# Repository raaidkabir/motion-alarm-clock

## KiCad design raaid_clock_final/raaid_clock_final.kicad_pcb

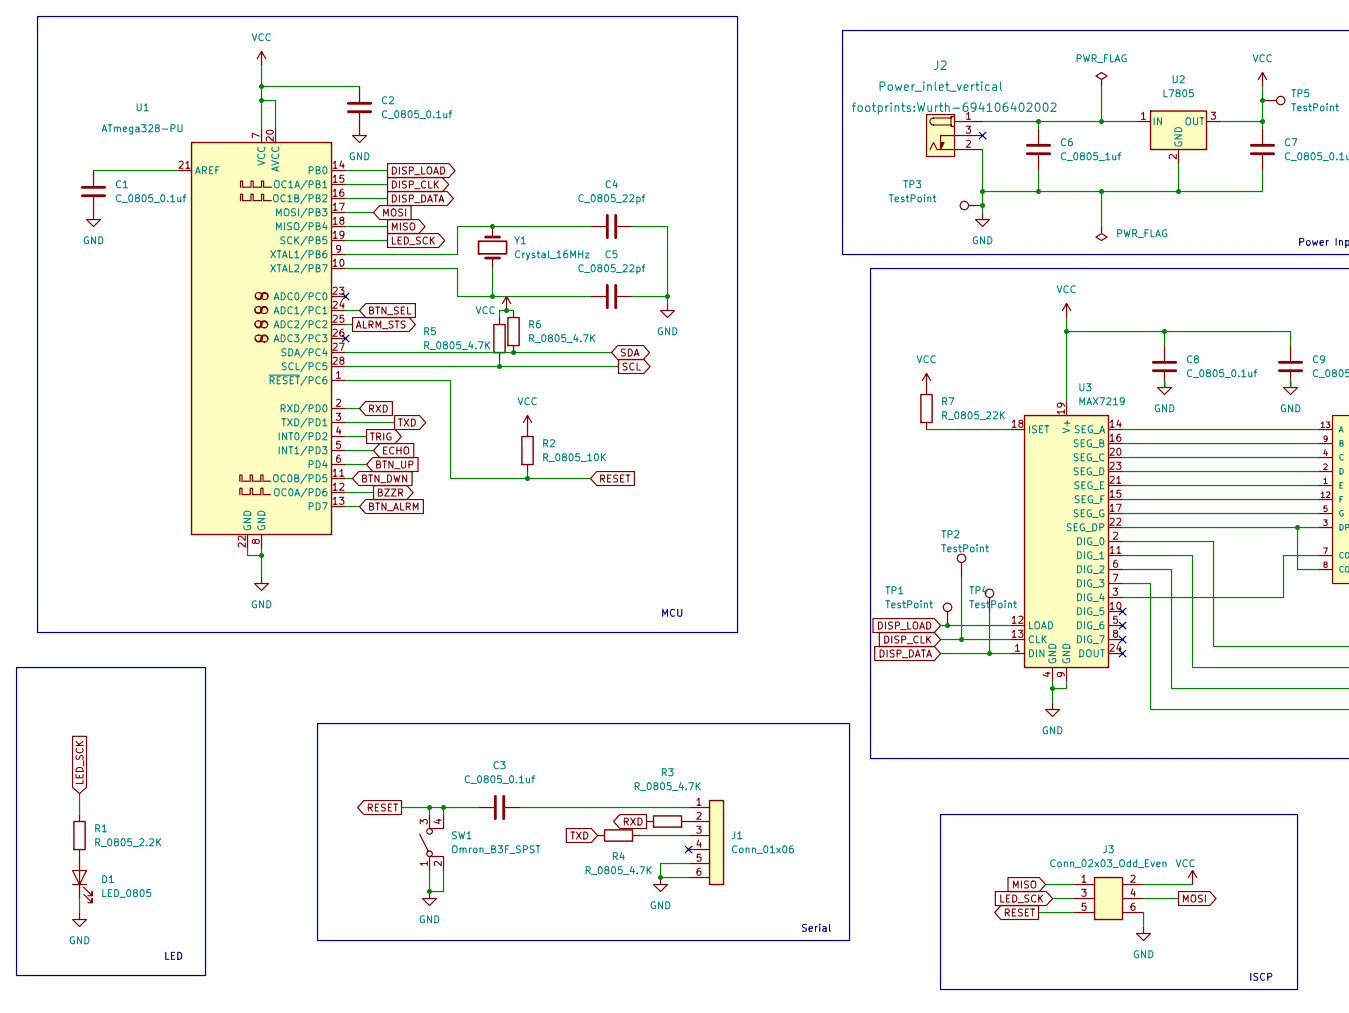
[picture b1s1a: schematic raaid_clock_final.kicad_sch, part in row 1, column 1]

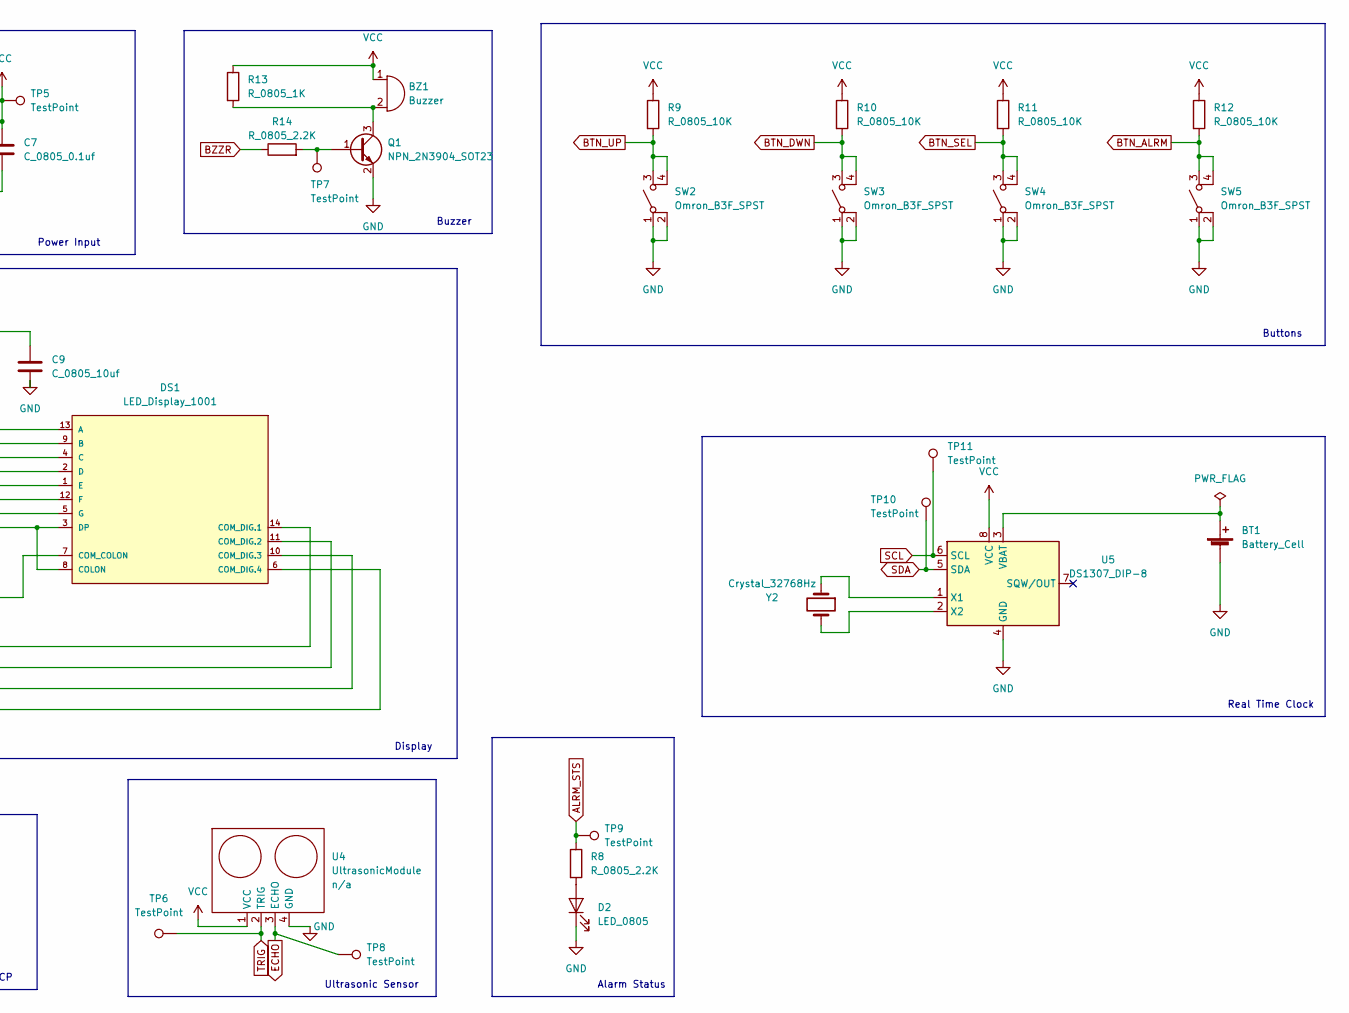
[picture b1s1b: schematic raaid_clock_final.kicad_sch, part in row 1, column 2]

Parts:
BT1: Battery_Cell; BatteryHolder_Keystone_106_1x20mm; MPN BS-7; Digikey PN BS-7-ND
BZ1: Buzzer; Buzzer_TDK_PS1240P02BT_D12.2mm_H6.5mm; MPN PS1420P02CT; Digikey PN 445-2526-1-ND
C1, C2, C3, C7, C8: C_0805_0.1uf; C_0805_2012Metric; Voltage N/A; Tolerance N/A; MPN 08055C104KAT2A; Digikey PN 478-1395-1-ND
C4, C5: C_0805_22pf; C_0805_2012Metric; Voltage N/A; Tolerance N/A; MPN CC0805JRNPO9BN220; Digikey PN 311-1103-1-ND
C6: C_0805_1uf; C_0805_2012Metric; Voltage N/A; Tolerance N/A; MPN CC0805KKX7R8BB105; Digikey PN 311-1456-1-ND
C9: C_0805_10uf; C_0805_2012Metric; Voltage N/A; Tolerance N/A; MPN GRM21BR61E106KA73L; Digikey PN 490-5523-1-ND
D1, D2: LED_0805; LED_0805_2012Metric; MPN 150080RS75000; Digikey PN 732-4984-1-ND
DS1: LED_Display_1001; Adafruit-1001-0-0-MFG; forward voltage 3.2V; reverse voltage 5V; mouser part number 485-1001; digikey description WHITE 7-SEGMENT CLOCK DISPLAY
J1: Conn_01x06; PinHeader_1x06_P2.54mm_Vertical; MPN 61300611121; Digikey PN 732-5319-ND
J2: Power_inlet_vertical; Wurth-694106402002; MPN 694106402002; Digikey PN 732-5931-ND
J3: Conn_02x03_Odd_Even; PinHeader_2x03_P2.54mm_Vertical; MPN PRPC003DAAN-RC; Digikey PN S2011EC-03-ND
Q1: NPN_2N3904_SOT23; SOT-23; MPN CMPT3904E TR PBFREE; Digikey PN 1514-CMPT3904ETRPBFREECT-ND
R1, R8, R14: R_0805_2.2K; R_0805_2012Metric; Tolerance N/A; MPN N/A; Digikey PN 311-2.20KCRCT-ND
R2, R9, R10, R11, R12: R_0805_10K; R_0805_2012Metric; Tolerance N/A; MPN RC0805FR-0710KL; Digikey PN 311-10.0KCRCT-ND
R3, R4, R5, R6: R_0805_4.7K; R_0805_2012Metric; Tolerance N/A; MPN RC0805FR-074K7L; Digikey PN 311-4.70KCRCT-ND
R7: R_0805_22K; R_0805_2012Metric; Tolerance N/A; MPN RC0805FR-0722KL; Digikey PN 311-22.0KCRCT-ND
R13: R_0805_1K; R_0805_2012Metric; Tolerance N/A; Mouser PN N/A; Digikey PN RC0805FR-0710KL
SW1, SW2, SW3, SW4, SW5: Omron_B3F_SPST; SW_SPST_Omron_B3FS-100xP; MPN B3FS-1000P; Digikey PN SW423CT-ND
TP1, TP2, TP3, TP4, TP5, TP6, TP7, TP8, TP9, TP10, TP11: TestPoint; TestPoint_THTPad_D2.0mm_Drill1.0mm
U1: ATmega328-PU; DIP-28_W7.62mm; MPN ED281DT; Digikey PN ED3050-5-ND
U2: L7805; TO-252-2; MPN L7805CDT-TR; Digikey PN 497-7255-1-ND
U3: MAX7219; DIP-24_W7.62mm; MPN ED241DT; Digikey PN ED3049-5-ND
U4: UltrasonicModule; HC-SR04_Horiz; Digikey PN n/a
U5: DS1307_DIP-8; DIP-8_W7.62mm; MPN A 08-LC-TT; Digikey PN AE9986-ND
Y1: Crystal_16MHz; Crystal_SMD_HC49-SD; MPN ECS-160-20-5PXDN-TR; Digikey PN XC1299CT-ND
Y2: Crystal_32768Hz; Crystal_SMD_2Pin_3.2x1.5mm; MPN Q 0,032768-JTX310-12,5-20-T1-HMR-50K-LF; Digikey PN 1908-1314-1-ND

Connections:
ALRM_STS: R8.1, TP9.1, U1.25 (ADC2/PC2)
BTN_ALRM: R12.2, SW5.3 (B), SW5.4 (B), U1.13 (PD7)
BTN_DWN: R10.2, SW3.3 (B), SW3.4 (B), U1.11 (OC0B/PD5)
BTN_SEL: R11.2, SW4.3 (B), SW4.4 (B), U1.24 (ADC1/PC1)
BTN_UP: R9.2, SW2.3 (B), SW2.4 (B), U1.6 (PD4)
BZZR: R14.1, U1.12 (OC0A/PD6)
DISP_CLK: TP2.1, U1.15 (OC1A/PB1), U3.13 (CLK)
DISP_DATA: TP4.1, U1.16 (OC1B/PB2), U3.1 (DIN)
DISP_LOAD: TP1.1, U1.14 (PB0), U3.12 (LOAD)
ECHO: TP8.1, U1.5 (INT1/PD3), U4.3 (ECHO)
GND: BT1.2 (-), C1.2, C2.2, C4.2, C5.2, C6.2, C7.2, C8.2, C9.2, D1.1 (K), D2.1 (K), J1.5, J1.6, J2.2 (OUT), J3.6, Q1.2 (E), SW1.1 (A), SW1.2 (A), SW2.1 (A), SW2.2 (A), SW3.1 (A), SW3.2 (A), SW4.1 (A), SW4.2 (A), SW5.1 (A), SW5.2 (A), TP3.1, U1.8 (GND), U1.22 (GND), U2.2 (GND), U3.4 (GND), U3.9 (GND), U4.4 (GND), U5.4 (GND)
LED_SCK: J3.3, R1.1, U1.19 (SCK/PB5)
MISO: J3.1, U1.18 (MISO/PB4)
MOSI: J3.4, U1.17 (MOSI/PB3)
unnamed: BT1.1 (+), U5.3 (VBAT)
unnamed: BZ1.2 (+), Q1.3 (C), R13.2
unnamed: C1.1, U1.21 (AREF)
unnamed: C3.1, J1.1
unnamed: C4.1, U1.9 (XTAL1/PB6), Y1.2
unnamed: C5.1, U1.10 (XTAL2/PB7), Y1.1
unnamed: C6.1, J2.1 (POLE), U2.1 (IN)
unnamed: D1.2 (A), R1.2
unnamed: D2.2 (A), R8.2
unnamed: DS1.1 (E), U3.21 (SEG_E)
unnamed: DS1.2 (D), U3.23 (SEG_D)
unnamed: DS1.3 (DP), DS1.8 (COLON), U3.22 (SEG_DP)
unnamed: DS1.4 (C), U3.20 (SEG_C)
unnamed: DS1.5 (G), U3.17 (SEG_G)
unnamed: DS1.6 (COM_DIG.4), U3.7 (DIG_3)
unnamed: DS1.7 (COM_COLON), U3.3 (DIG_4)
unnamed: DS1.9 (B), U3.16 (SEG_B)
unnamed: DS1.10 (COM_DIG.3), U3.6 (DIG_2)
unnamed: DS1.11 (COM_DIG.2), U3.11 (DIG_1)
unnamed: DS1.12 (F), U3.15 (SEG_F)
unnamed: DS1.13 (A), U3.14 (SEG_A)
unnamed: DS1.14 (COM_DIG.1), U3.2 (DIG_0)
unnamed: J1.2, R3.2
unnamed: J1.3, R4.2
unnamed: Q1.1 (B), R14.2, TP7.1
unnamed: R7.2, U3.18 (ISET)
unnamed: U5.1 (X1), Y2.1
unnamed: U5.2 (X2), Y2.2
RESET: C3.2, J3.5, R2.2, SW1.3 (B), SW1.4 (B), U1.1 (~RESET/PC6)
RXD: R3.1, U1.2 (RXD/PD0)
SCL: R5.2, TP11.1, U1.28 (SCL/PC5), U5.6 (SCL)
SDA: R6.2, TP10.1, U1.27 (SDA/PC4), U5.5 (SDA)
TRIG: TP6.1, U1.4 (INT0/PD2), U4.2 (TRIG)
TXD: R4.1, U1.3 (TXD/PD1)
VCC: BZ1.1 (-), C2.1, C7.1, C8.1, C9.1, J3.2, R2.1, R5.1, R6.1, R7.1, R9.1, R10.1, R11.1, R12.1, R13.1, TP5.1, U1.7 (VCC), U1.20 (AVCC), U2.3 (OUT), U3.19 (V+), U4.1 (VCC), U5.8 (VCC)

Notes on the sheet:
MCU
Buzzer
Power Input
LED
Ultrasonic Sensor
Alarm Status
ISCP
Display
Serial
Real Time Clock
Buttons

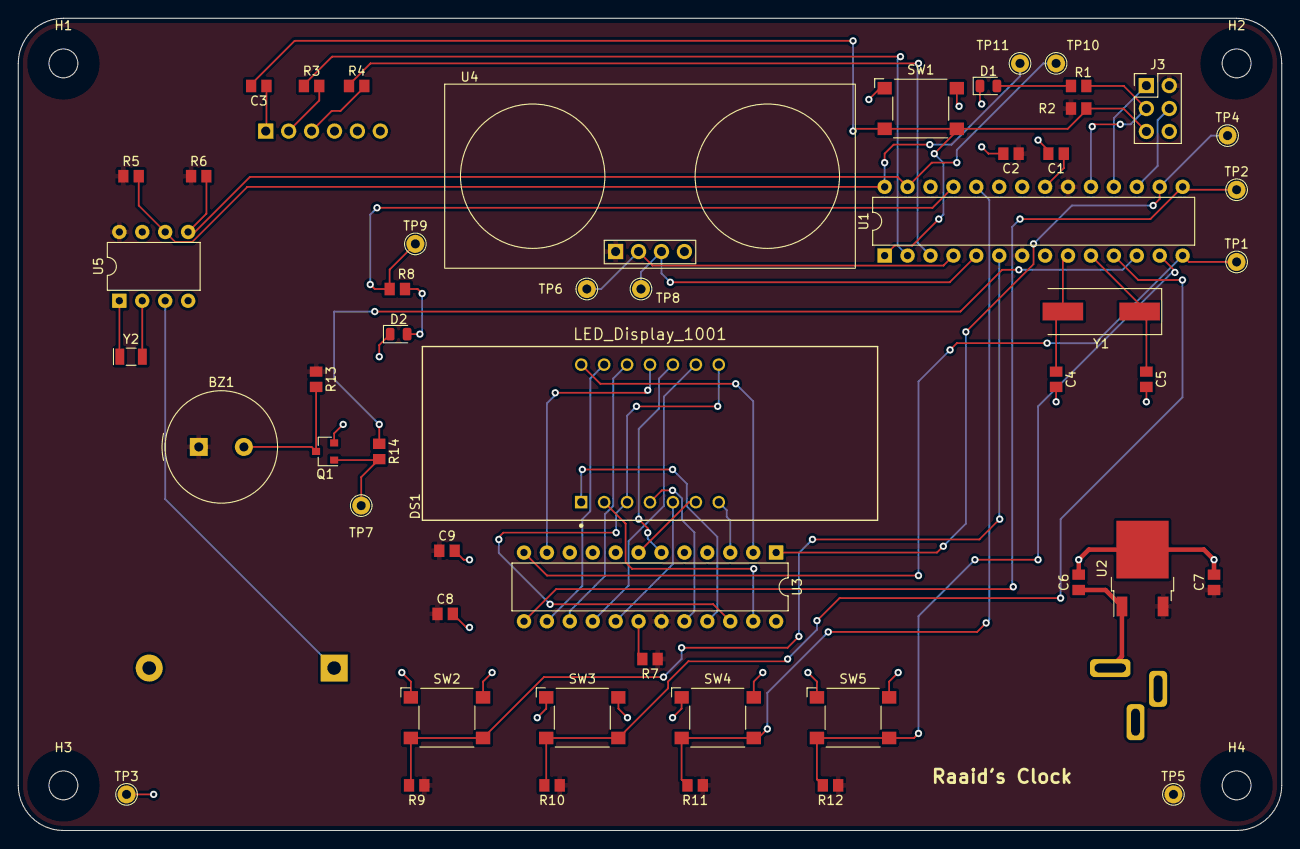
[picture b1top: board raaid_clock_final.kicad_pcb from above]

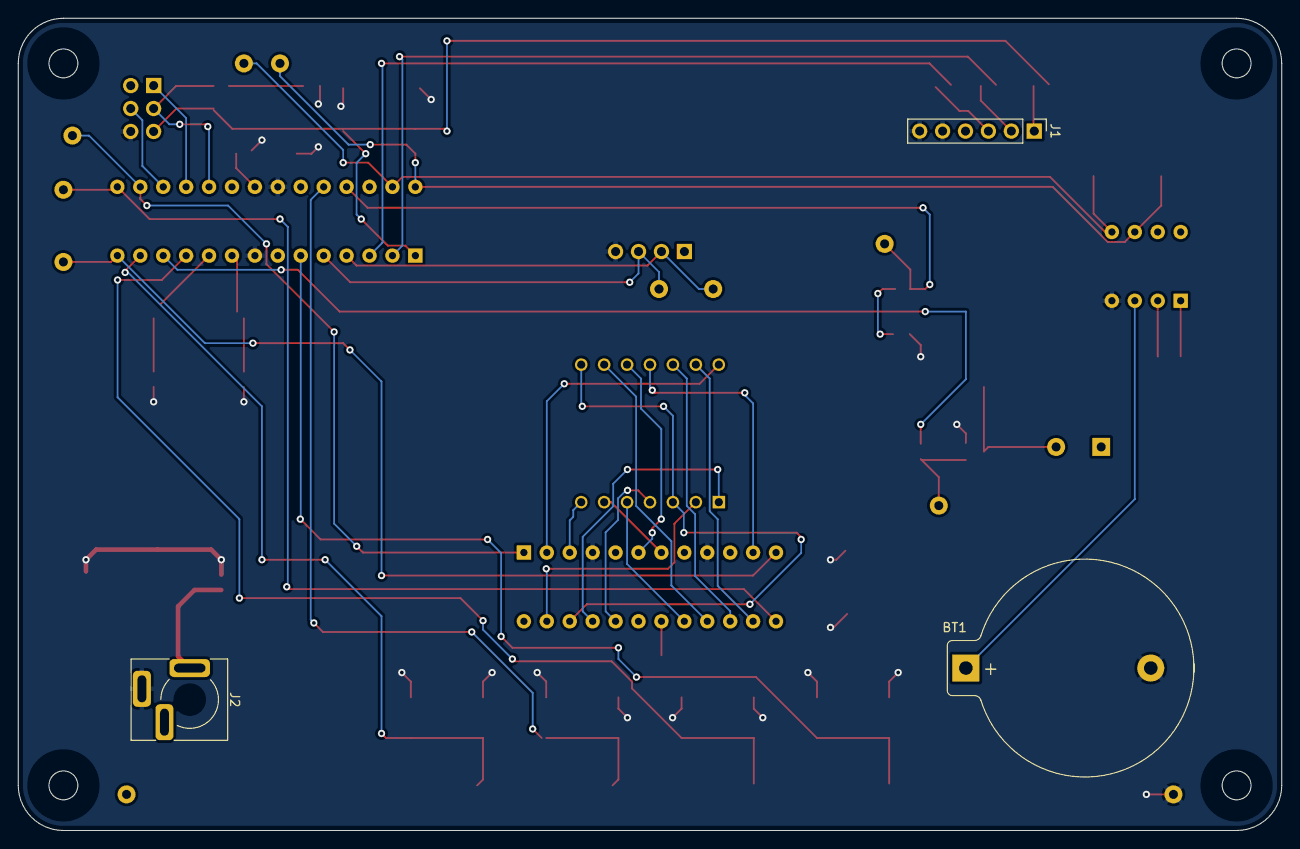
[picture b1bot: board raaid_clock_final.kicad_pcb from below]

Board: 2 copper layers, 140.0 x 90.0 mm, 59 parts (3 on the bottom side), 49 nets.

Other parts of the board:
H1, H2, H3, H4: MountingHole; MountingHole_3.2mm_M3

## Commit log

2022-07-20 added STEP file
2022-07-21 moved inlet; redid gerbers
2022-07-21 step file added
